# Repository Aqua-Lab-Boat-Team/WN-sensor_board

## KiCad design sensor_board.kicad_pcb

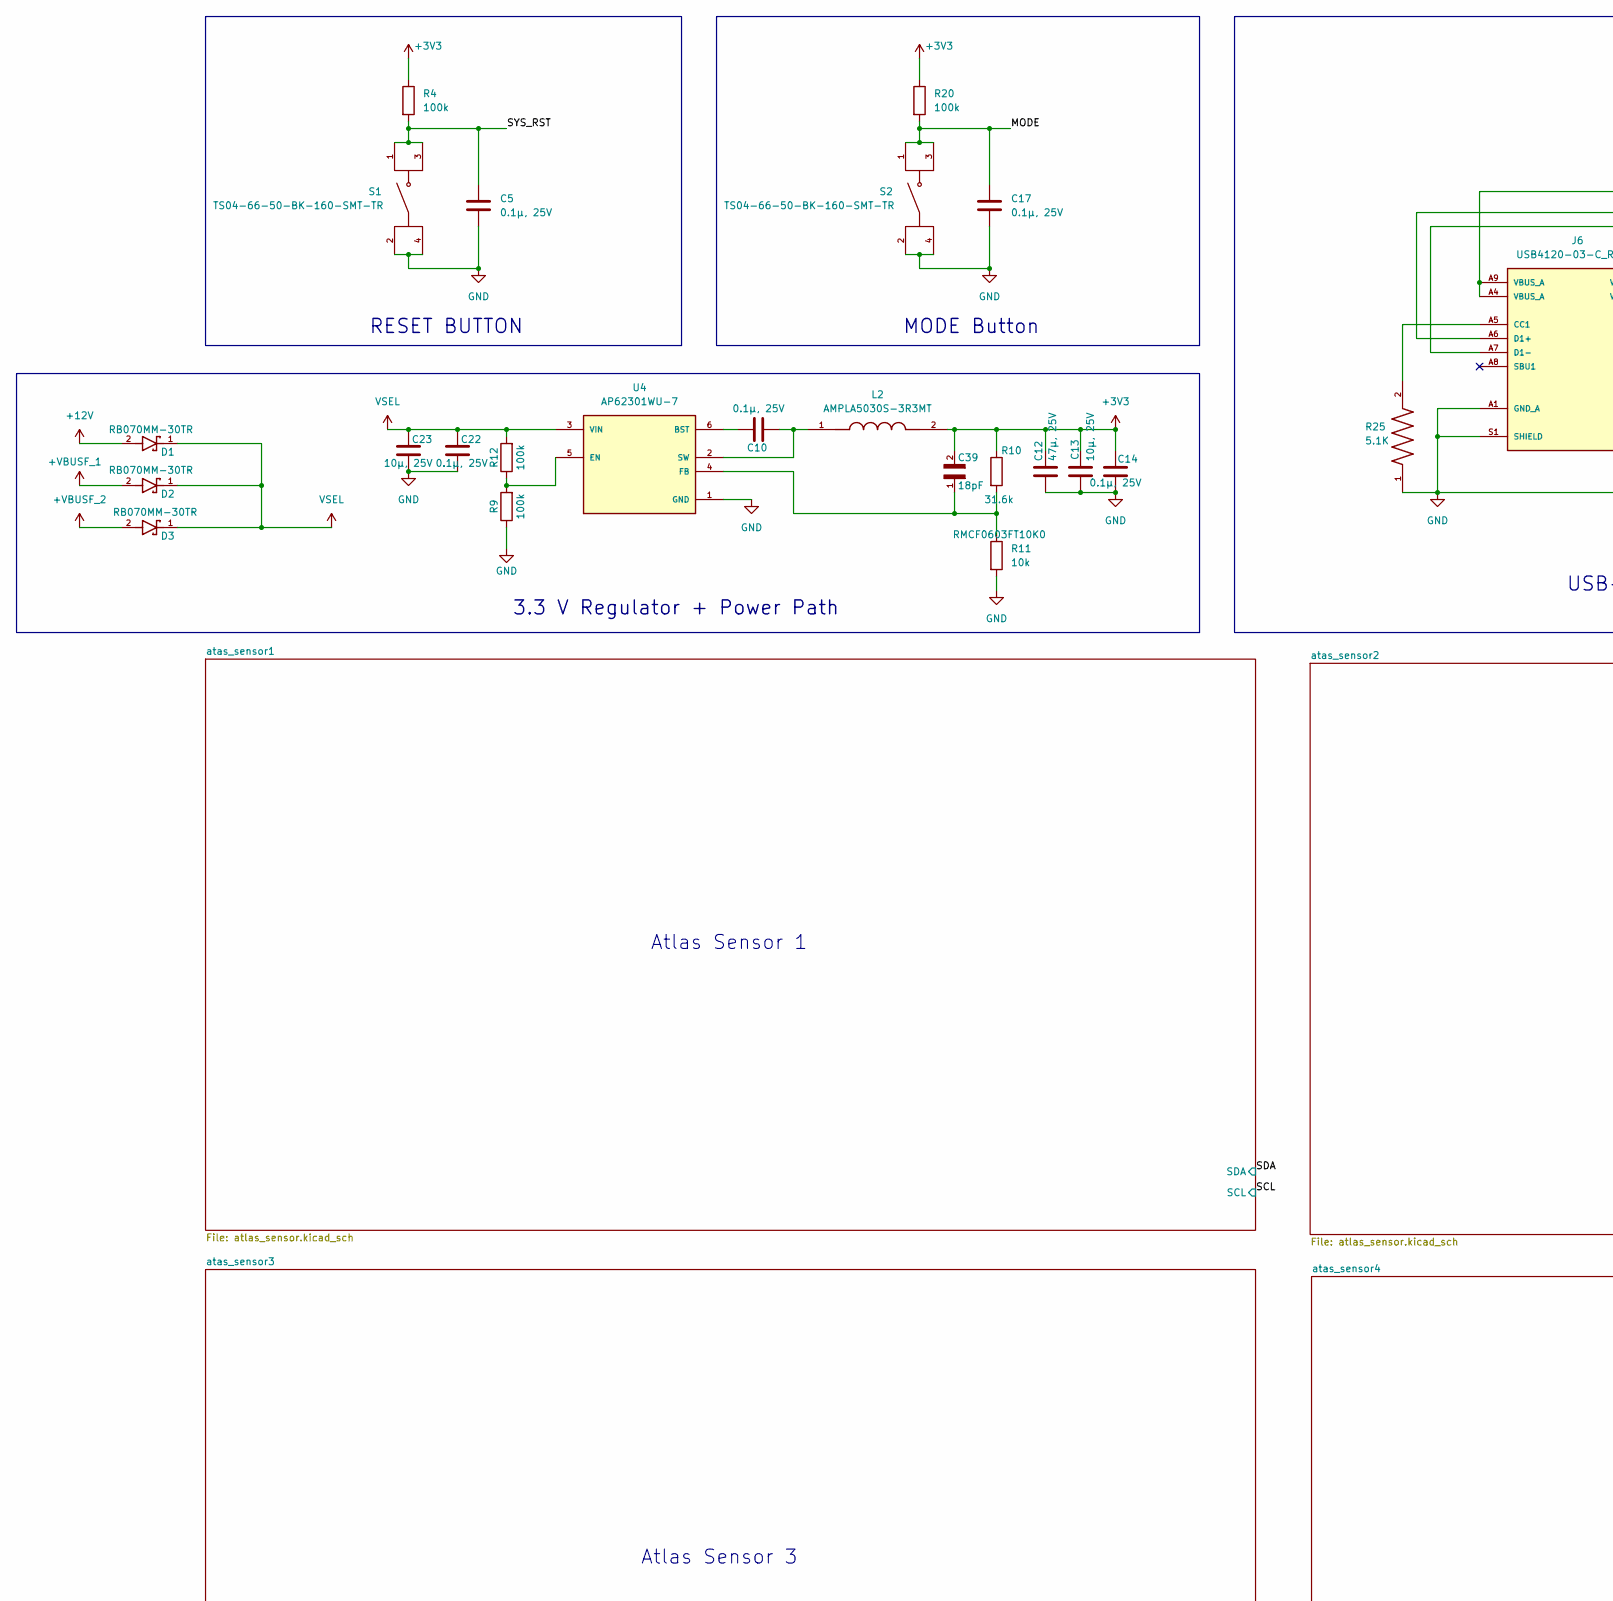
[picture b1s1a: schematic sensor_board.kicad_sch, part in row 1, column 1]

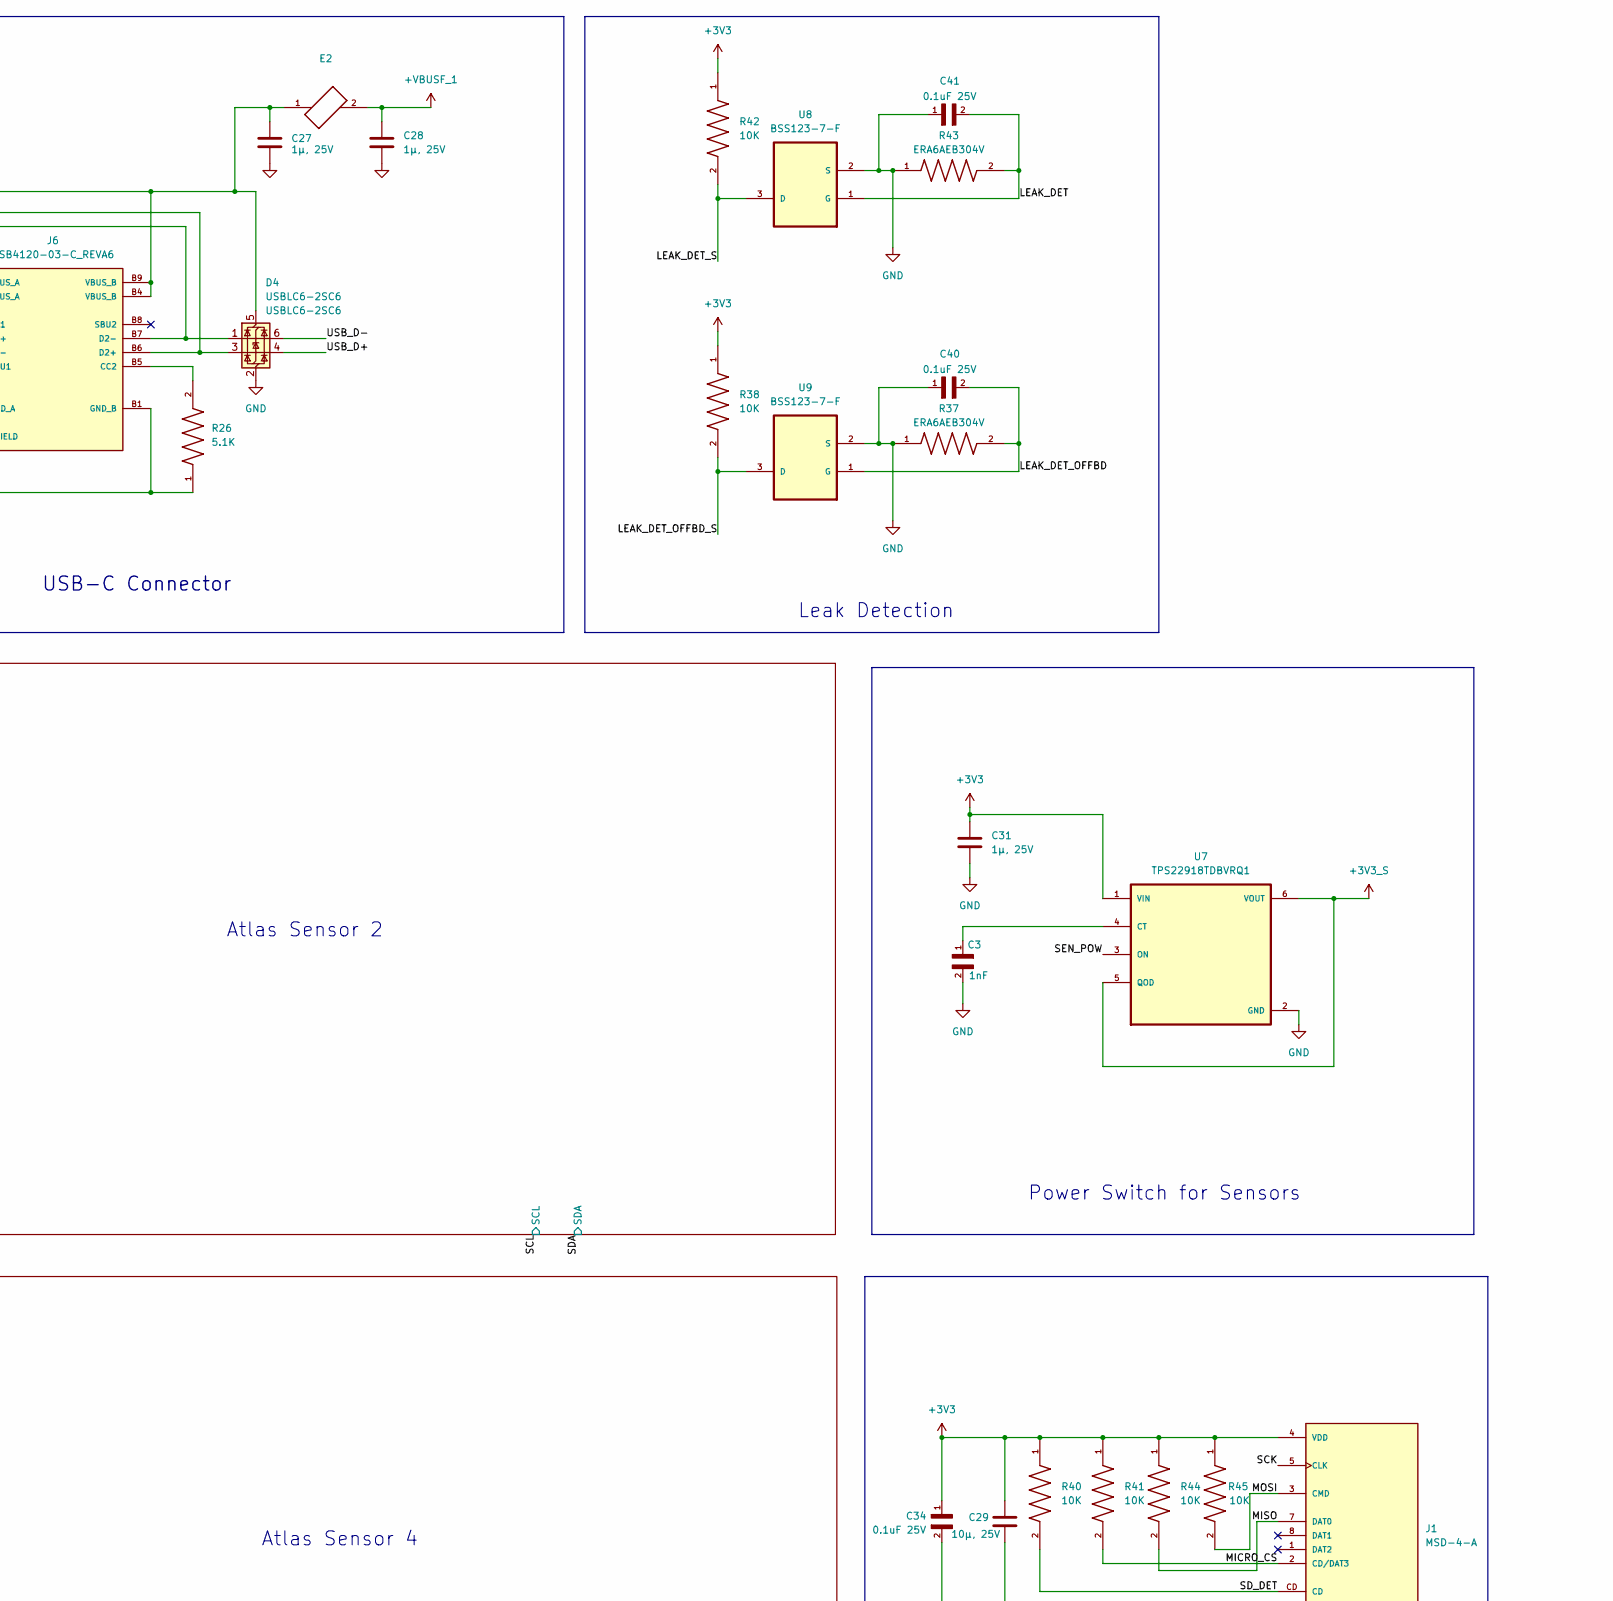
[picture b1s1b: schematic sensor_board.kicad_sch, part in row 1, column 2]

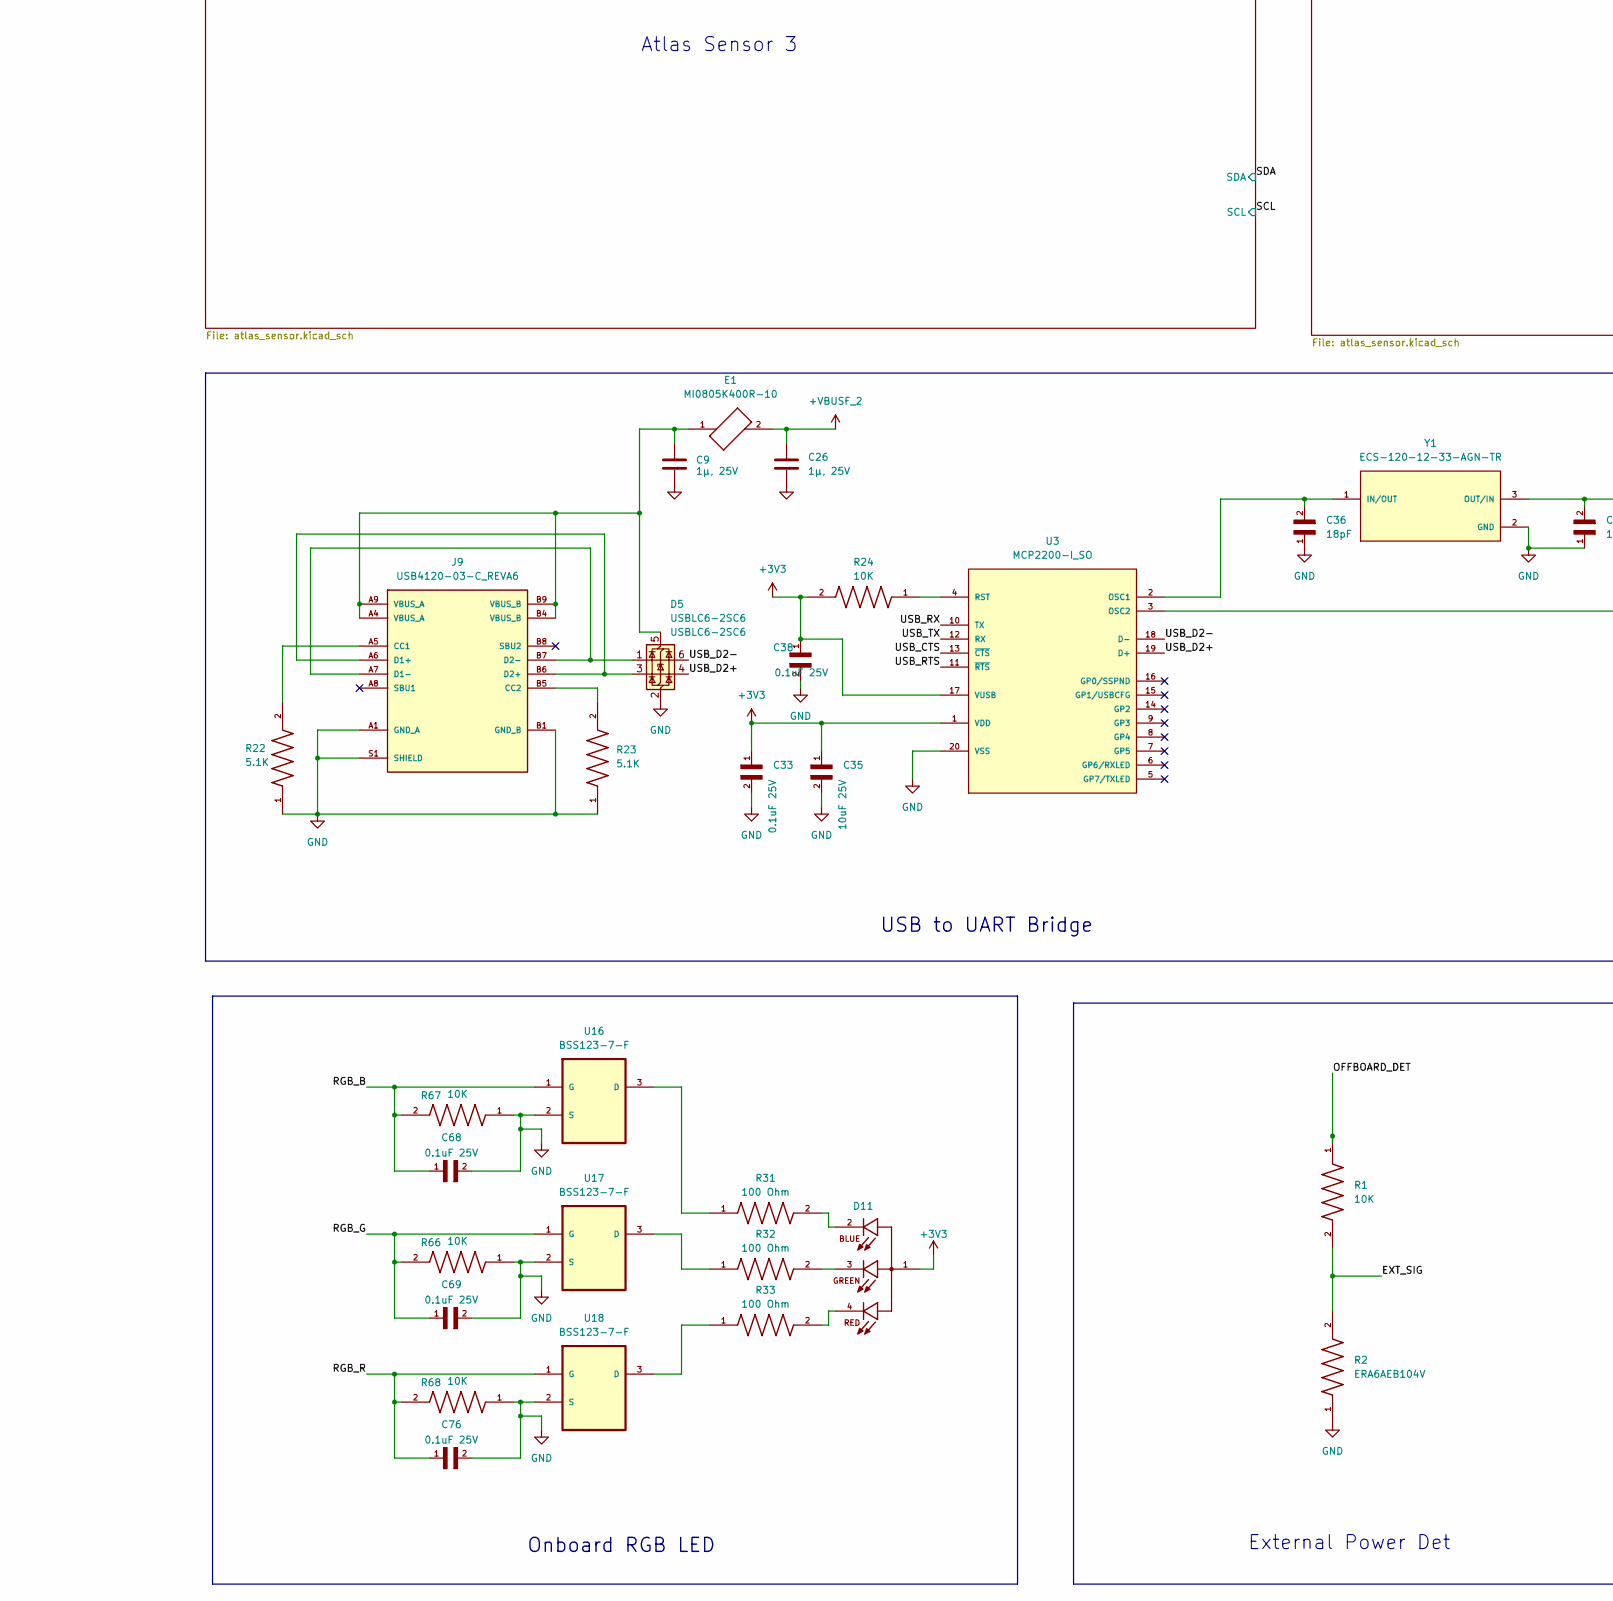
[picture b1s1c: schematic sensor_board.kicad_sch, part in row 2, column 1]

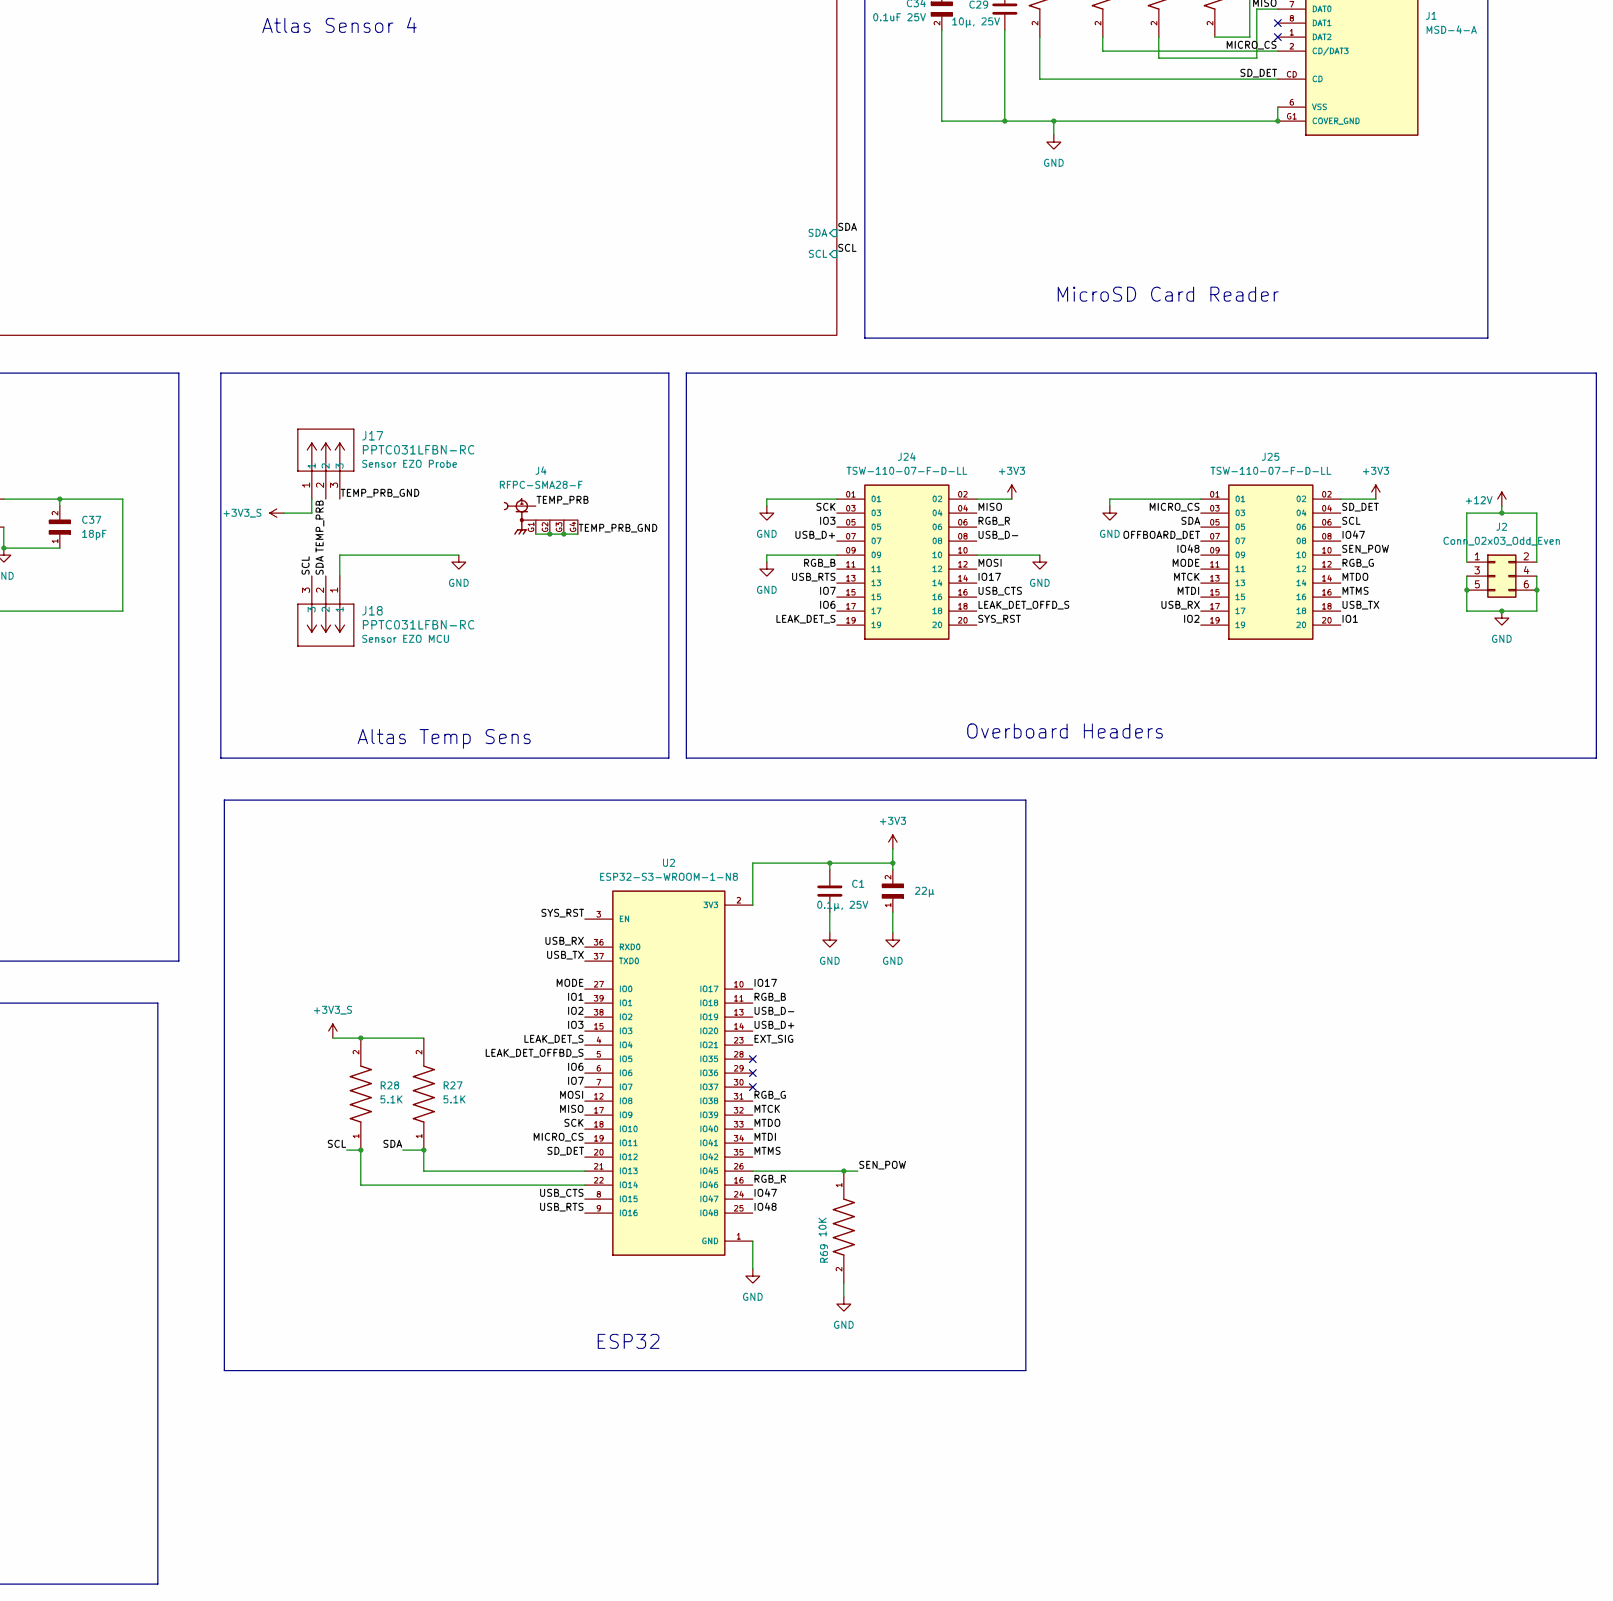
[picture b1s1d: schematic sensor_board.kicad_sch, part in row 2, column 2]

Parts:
C1, C5, C10, C14, C17, C22: 0.1µ, 25V; CAPC2012X95N
C2: 22µ; CAPC1608X105N
C3: 1nF; CAPC1608X90
C9, C26, C27, C28, C31: 1µ, 25V; CAPC2012X145N
C12: 47µ, 25V; CAPC3216X180N
C13, C23, C29: 10µ, 25V; CAPC2012X145N
C33, C34, C38, C40, C41, C68, C69, C76: 0.1uF 25V; CAPC2012X95N
C35: 10uF 25V; CAPC2012X145N
C36, C37, C39: 18pF; CAPC1608X90N
D1, D2, D3: RB070MM-30TR; DIO_RB070MM-30TR
D4, D5: USBLC6-2SC6; SOT-23-6
D11: CLMVC-FKA-CL1D1L71BB7C3C3; LED_CLMVC-FKA-CL1D1L71BB7C3C3; PARTREV 14
E1, E2: MI0805K400R-10; FB_MI0805K400R-10
J1: MSD-4-A; CUI_MSD-4-A; PARTREV 1.0
J2: Conn_02x03_Odd_Even; SULLINS_PPTC032LFBN-RC
J4: RFPC-SMA28-F; GRADCONN_RFPC-SMA28-F; PARTREV 1.0
J6, J9: USB4120-03-C_REVA6; GCT_USB4120-03-C_REVA6; PARTREV A6
J17, J18: PPTC031LFBN-RC; CONN_PPTC031_SUL
J24, J25: TSW-110-07-F-D-LL; SAMTEC_TSW-110-07-F-D-LL; PARTREV R
L2: AMPLA5030S-3R3MT; IND_AMPLA5030S-3R3MT; PARTREV 9/23/2019
R1, R24, R38, R40, R41, R42, R44, R45, R66, R67, R68, R69: 10K; RES_ERA6AEB103V; PARTREV 3/1/2020
R2: ERA6AEB104V; RES_ERA6AEB104V; PARTREV 3/1/2020
R4, R9, R12, R20: 100k; RES_ERA6AEB104V
R10: 31.6k; RES_ERA6AEB3162V
R11: 10k; RES_ERA6AEB103V
R22, R23, R25, R26, R27, R28: 5.1K; RESC1508X55N
R31, R32, R33: 100 Ohm; RES_ERJ3EKF1000V; PARTREV 3/1/2020
R37, R43: ERA6AEB304V; RES_ERA6AEB304V; PARTREV 3/1/2020
S1, S2: TS04-66-50-BK-160-SMT-TR; SW_TS04-66-50-BK-160-SMT-TR; PARTREV 1.04mm
U2: ESP32-S3-WROOM-1-N8; XCVR_ESP32-S3-WROOM-1-N8
U3: MCP2200-I_SO; SOIC20; MANUFACTURER_PART_NUMBER mcp2200-i/so
U4: AP62301WU-7; SOT95P280X100-6N; PARTREV Rev. 3 - 2
U7: TPS22918TDBVRQ1; SOT95P280X145-6N
U8, U9, U16, U17, U18: BSS123-7-F; SOT95P240X110-3N; MPN BSS123-7-F
Y1: ECS-120-12-33-AGN-TR; XTAL_ECS-120-12-33-AGN-TR

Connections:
+3V3: C1.1, C2.2, C12.1, C13.1, C14.1, C29.2, C31.1, C33.1, C34.1, C35.1, C38.1, C39.2, D11.1, J1.4 (VDD), J24.02, J25.02, L2.2, R4.1, R10.1, R20.1, R24.2, R38.1, R40.1, R41.1, R42.1, R44.1, R45.1, U2.2 (3V3), U3.1 (VDD), U3.17 (VUSB), U7.1 (VIN)
+3V3_S: J17.1, R27.2, R28.2, U7.5 (QOD), U7.6 (VOUT); also elsewhere on the board
+12V: D1.2, J2.1, J2.2
+VBUSF_1: C28.1, D2.2, E2.2
+VBUSF_2: C26.1, D3.2, E1.2
/IO1: J25.20, U2.39 (IO1)
/IO2: J25.19, U2.38 (IO2)
/IO3: J24.05, U2.15 (IO3)
/IO6: J24.17, U2.6 (IO6)
/IO7: J24.15, U2.7 (IO7)
/IO17: J24.14, U2.10 (IO17)
/IO47: J25.08, U2.24 (IO47)
/IO48: J25.09, U2.25 (IO48)
/LEAK_DET: C41.2, R43.2, U8.1 (G)
/LEAK_DET_OFFBD: C40.2, R37.2, U9.1 (G)
/LEAK_DET_S: J24.19, R42.2, U2.4 (IO4), U8.3 (D)
/MICRO_CS: J1.2 (CD/DAT3), J25.03, R41.2, U2.19 (IO11)
/MISO: J1.7 (DAT0), J24.04, R44.2, U2.17 (IO9)
/MODE: C17.1, J25.11, R20.2, S2.1, S2.3, U2.27 (IO0)
/MOSI: J1.3 (CMD), J24.12, R45.2, U2.12 (IO8)
/MTCK: J25.13, U2.32 (IO39)
/MTDI: J25.15, U2.34 (IO41)
/MTDO: J25.14, U2.33 (IO40)
/MTMS: J25.16, U2.35 (IO42)
/RGB_B: C68.1, J24.11, R67.2, U2.11 (IO18), U16.1 (G)
/RGB_G: C69.1, J25.12, R66.2, U2.31 (IO38), U17.1 (G)
/RGB_R: C76.1, J24.06, R68.2, U2.16 (IO46), U18.1 (G)
/SCK: J1.5 (CLK), J24.03, U2.18 (IO10)
/SCL: J18.3, J25.06, R28.1, U2.22 (IO14); also elsewhere on the board
/SDA: J18.2, J25.05, R27.1, U2.21 (IO13); also elsewhere on the board
/SD_DET: J1.CD, J25.04, R40.2, U2.20 (IO12)
/SEN_POW: J25.10, R69.1, U2.26 (IO45), U7.3 (ON)
/SYS_RST: C5.1, J24.20, R4.2, S1.1, S1.3, U2.3 (EN)
/TEMP_PRB: J4.1, J17.2
/TEMP_PRB_GND: J4.G1, J4.G2, J4.G3, J4.G4, J17.3
/USB_CTS: J24.16, U2.8 (IO15), U3.13 (~CTS)
/USB_D2+: D5.4 (I/O2), U3.19 (D+)
/USB_D2-: D5.6 (I/O1), U3.18 (D-)
/USB_D+: D4.4 (I/O2), J24.07, U2.14 (IO20)
/USB_D-: D4.6 (I/O1), J24.08, U2.13 (IO19)
/USB_RTS: J24.13, U2.9 (IO16), U3.11 (~RTS)
/USB_RX: J25.17, U2.36 (RXD0), U3.10 (TX)
/USB_TX: J25.18, U2.37 (TXD0), U3.12 (RX)
GND: C1.2, C2.1, C3.2, C5.2, C9.2, C12.2, C13.2, C14.2, C17.2, C22.2, C23.2, C26.2, C27.2, C28.2, C29.1, C31.2, C33.2, C34.2, C35.2, C36.1, C37.1, C38.2, C40.1, C41.1, C68.2, C69.2, C76.2, D4.2 (GND), D5.2 (GND), J1.6 (VSS), J1.G1 (COVER_GND), J1.G2 (COVER_GND), J1.G3 (COVER_GND), J1.G4 (COVER_GND), J2.3, J2.4, J2.5, J2.6, J6.A1 (GND_A), J6.A12 (GND_A), J6.B1 (GND_B), J6.B12 (GND_B), J6.S1 (SHIELD), J6.S2 (SHIELD), J6.S3 (SHIELD), J6.S4 (SHIELD), J9.A1 (GND_A), J9.A12 (GND_A), J9.B1 (GND_B), J9.B12 (GND_B), J9.S1 (SHIELD), J9.S2 (SHIELD), J9.S3 (SHIELD), J9.S4 (SHIELD), J18.1, J24.01, J24.09, J24.10, J25.01, R2.1, R9.1, R11.2, R22.1, R23.1, R25.1, R26.1, R37.1, R43.1, R66.1, R67.1, R68.1, R69.2, S1.2, S1.4, S2.2, S2.4, U2.1 (GND), U2.40 (GND), U2.41, U2.41_1 (GND), U2.41_2 (GND), U2.41_3 (GND), U2.41_4 (GND), U2.41_5 (GND), U2.41_6 (GND), U2.41_7 (GND), U2.41_8 (GND), U2.41_9 (GND), U3.20 (VSS), U4.1 (GND), U7.2 (GND), U8.2 (S), U9.2 (S), U16.2 (S), U17.2 (S), U18.2 (S), Y1.2 (GND), Y1.4 (GND); also elsewhere on the board
unnamed: C27.1, D4.5 (VBUS), E2.1, J6.A4 (VBUS_A), J6.A9 (VBUS_A), J6.B4 (VBUS_B), J6.B9 (VBUS_B)
unnamed: C9.1, D5.5 (VBUS), E1.1, J9.A4 (VBUS_A), J9.A9 (VBUS_A), J9.B4 (VBUS_B), J9.B9 (VBUS_B)
unnamed: D11.2, R31.2
unnamed: D11.3, R32.2
unnamed: D11.4, R33.2
unnamed: J6.A5 (CC1), R25.2
unnamed: J6.B5 (CC2), R26.2
unnamed: D4.3 (I/O2), J6.A6 (D1+), J6.B6 (D2+)
unnamed: D4.1 (I/O1), J6.A7 (D1-), J6.B7 (D2-)
unnamed: J9.A5 (CC1), R22.2
unnamed: J9.B5 (CC2), R23.2
unnamed: D5.3 (I/O2), J9.A6 (D1+), J9.B6 (D2+)
unnamed: D5.1 (I/O1), J9.A7 (D1-), J9.B7 (D2-)
unnamed: C36.2, U3.2 (OSC1), Y1.1 (IN/OUT)
unnamed: C37.2, U3.3 (OSC2), Y1.3 (OUT/IN)
unnamed: R24.1, U3.4 (RST)
unnamed: C10.1, U4.6 (BST)
unnamed: R9.2, R12.1, U4.5 (EN)
unnamed: C39.1, R10.2, R11.1, U4.4 (FB)
unnamed: C10.2, L2.1, U4.2 (SW)
unnamed: C3.1, U7.4 (CT)
unnamed: R31.1, U16.3 (D)
unnamed: R32.1, U17.3 (D)
unnamed: R33.1, U18.3 (D)
VSEL: C22.1, C23.1, D1.1, D2.1, D3.1, R12.2, U4.3 (VIN)

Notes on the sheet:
USB-C Connector
Atlas Sensor 1
ESP32
Leak Detection
Overboard Headers
MODE Button
RESET BUTTON
Onboard RGB LED
MicroSD Card Reader
External Power Det
Atlas Sensor 4
Atlas Sensor 2
Altas Temp Sens
USB to UART Bridge
Power Switch for Sensors
3.3 V Regulator + Power Path
Atlas Sensor 3

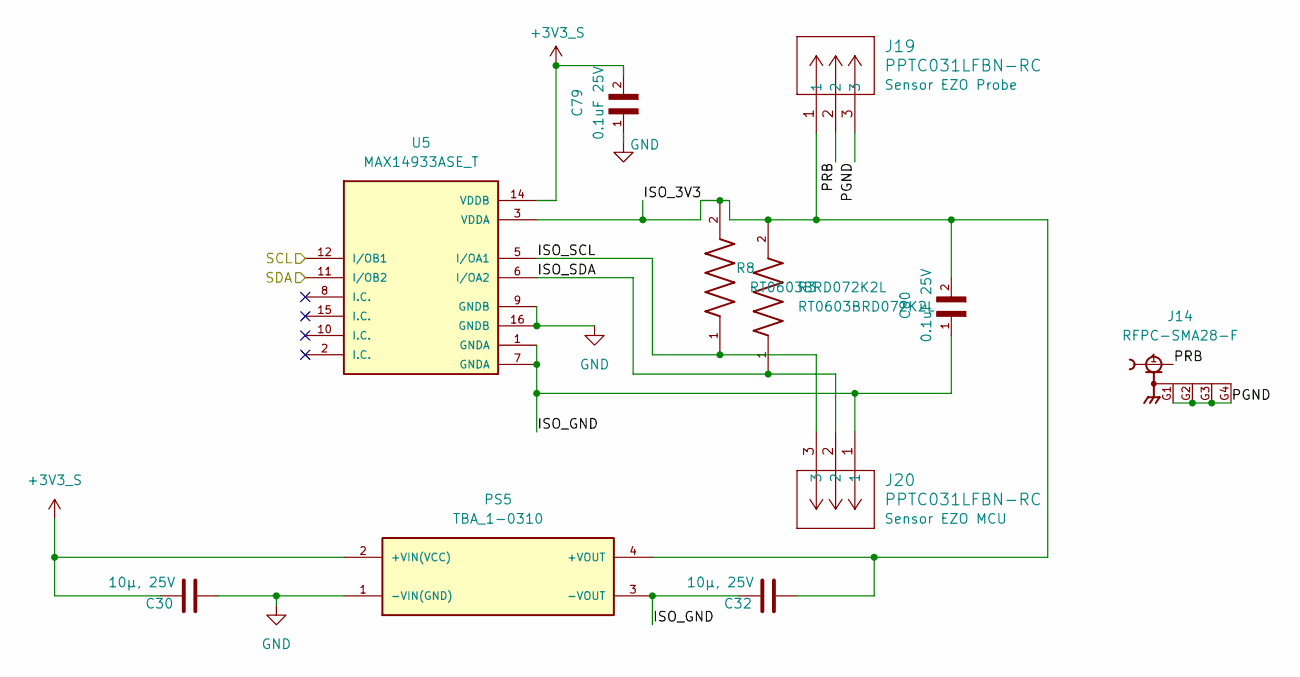
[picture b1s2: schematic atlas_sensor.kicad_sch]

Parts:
C30, C32: 10µ, 25V; CAPC2012X145N
C79, C80: 0.1uF 25V; CAPC2012X95N
J14: RFPC-SMA28-F; GRADCONN_RFPC-SMA28-F; PARTREV 1.0
J19, J20: PPTC031LFBN-RC; CONN_PPTC031_SUL
PS5: TBA_1-0310; CONV_TBA_1-0310; PARTREV April 19, 2021
R3, R8: RT0603BRD072K2L; RESC1608X55N
U5: MAX14933ASE_T; SOIC127P600X175-16N

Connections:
+3V3_S: C30.1, C79.2, PS5.2 (+VIN(VCC)), U5.14 (VDDB); also elsewhere on the board
/SCL: U5.12 (I/OB1); also elsewhere on the board
/SDA: U5.11 (I/OB2); also elsewhere on the board
/atas_sensor1/ISO_3V3: C32.2, C80.2, J19.1, PS5.4 (+VOUT), U5.3 (VDDA); also elsewhere on the board
/atas_sensor1/ISO_GND: C32.1, C80.1, J20.1, PS5.3 (-VOUT), U5.1 (GNDA), U5.7 (GNDA)
/atas_sensor1/ISO_SCL: J20.3, U5.5 (I/OA1); also elsewhere on the board
/atas_sensor1/ISO_SDA: J20.2, U5.6 (I/OA2); also elsewhere on the board
/atas_sensor1/PGND: J14.G1, J14.G2, J14.G3, J14.G4, J19.3
/atas_sensor1/PRB: J14.1, J19.2
GND: C30.2, C79.1, PS5.1 (-VIN(GND)), U5.9 (GNDB), U5.16 (GNDB); also elsewhere on the board

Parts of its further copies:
C42, C43, C44, C45, C46, C47: 10µ, 25V; CAPC2012X145N
C81, C82, C83, C84, C85, C86: 0.1uF 25V; CAPC2012X95N
J15, J16, J29: RFPC-SMA28-F; GRADCONN_RFPC-SMA28-F; PARTREV 1.0
J21, J22, J23, J26, J27, J28: PPTC031LFBN-RC; CONN_PPTC031_SUL
PS6, PS7, PS8: TBA_1-0310; CONV_TBA_1-0310; PARTREV April 19, 2021
U6, U10, U11: MAX14933ASE_T; SOIC127P600X175-16N

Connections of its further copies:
+3V3_S: C42.1, C44.1, C46.1, C81.2, C83.2, C85.2, PS6.2 (+VIN(VCC)), PS7.2 (+VIN(VCC)), PS8.2 (+VIN(VCC)), U6.14 (VDDB), U10.14 (VDDB), U11.14 (VDDB); also elsewhere on the board
/SCL: U6.12 (I/OB1), U10.12 (I/OB1), U11.12 (I/OB1); also elsewhere on the board
/SDA: U6.11 (I/OB2), U10.11 (I/OB2), U11.11 (I/OB2); also elsewhere on the board
/atas_sensor2/ISO_3V3: C47.2, C86.2, J27.1, PS8.4 (+VOUT), U11.3 (VDDA); also elsewhere on the board
/atas_sensor2/ISO_GND: C47.1, C86.1, J28.1, PS8.3 (-VOUT), U11.1 (GNDA), U11.7 (GNDA)
/atas_sensor2/ISO_SCL: J28.3, U11.5 (I/OA1); also elsewhere on the board
/atas_sensor2/ISO_SDA: J28.2, U11.6 (I/OA2); also elsewhere on the board
/atas_sensor2/PGND: J15.G1, J15.G2, J15.G3, J15.G4, J27.3
/atas_sensor2/PRB: J15.1, J27.2
/atas_sensor3/ISO_3V3: C43.2, C82.2, J21.1, PS6.4 (+VOUT), U6.3 (VDDA); also elsewhere on the board
/atas_sensor3/ISO_GND: C43.1, C82.1, J22.1, PS6.3 (-VOUT), U6.1 (GNDA), U6.7 (GNDA)
/atas_sensor3/ISO_SCL: J22.3, U6.5 (I/OA1); also elsewhere on the board
/atas_sensor3/ISO_SDA: J22.2, U6.6 (I/OA2); also elsewhere on the board
/atas_sensor3/PGND: J16.G1, J16.G2, J16.G3, J16.G4, J21.3
/atas_sensor3/PRB: J16.1, J21.2
/atas_sensor4/ISO_3V3: C45.2, C84.2, J23.1, PS7.4 (+VOUT), U10.3 (VDDA); also elsewhere on the board
/atas_sensor4/ISO_GND: C45.1, C84.1, J26.1, PS7.3 (-VOUT), U10.1 (GNDA), U10.7 (GNDA)
/atas_sensor4/ISO_SCL: J26.3, U10.5 (I/OA1); also elsewhere on the board
/atas_sensor4/ISO_SDA: J26.2, U10.6 (I/OA2); also elsewhere on the board
/atas_sensor4/PGND: J23.3, J29.G1, J29.G2, J29.G3, J29.G4
/atas_sensor4/PRB: J23.2, J29.1
GND: C42.2, C44.2, C46.2, C81.1, C83.1, C85.1, PS6.1 (-VIN(GND)), PS7.1 (-VIN(GND)), PS8.1 (-VIN(GND)), U6.9 (GNDB), U6.16 (GNDB), U10.9 (GNDB), U10.16 (GNDB), U11.9 (GNDB), U11.16 (GNDB); also elsewhere on the board

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
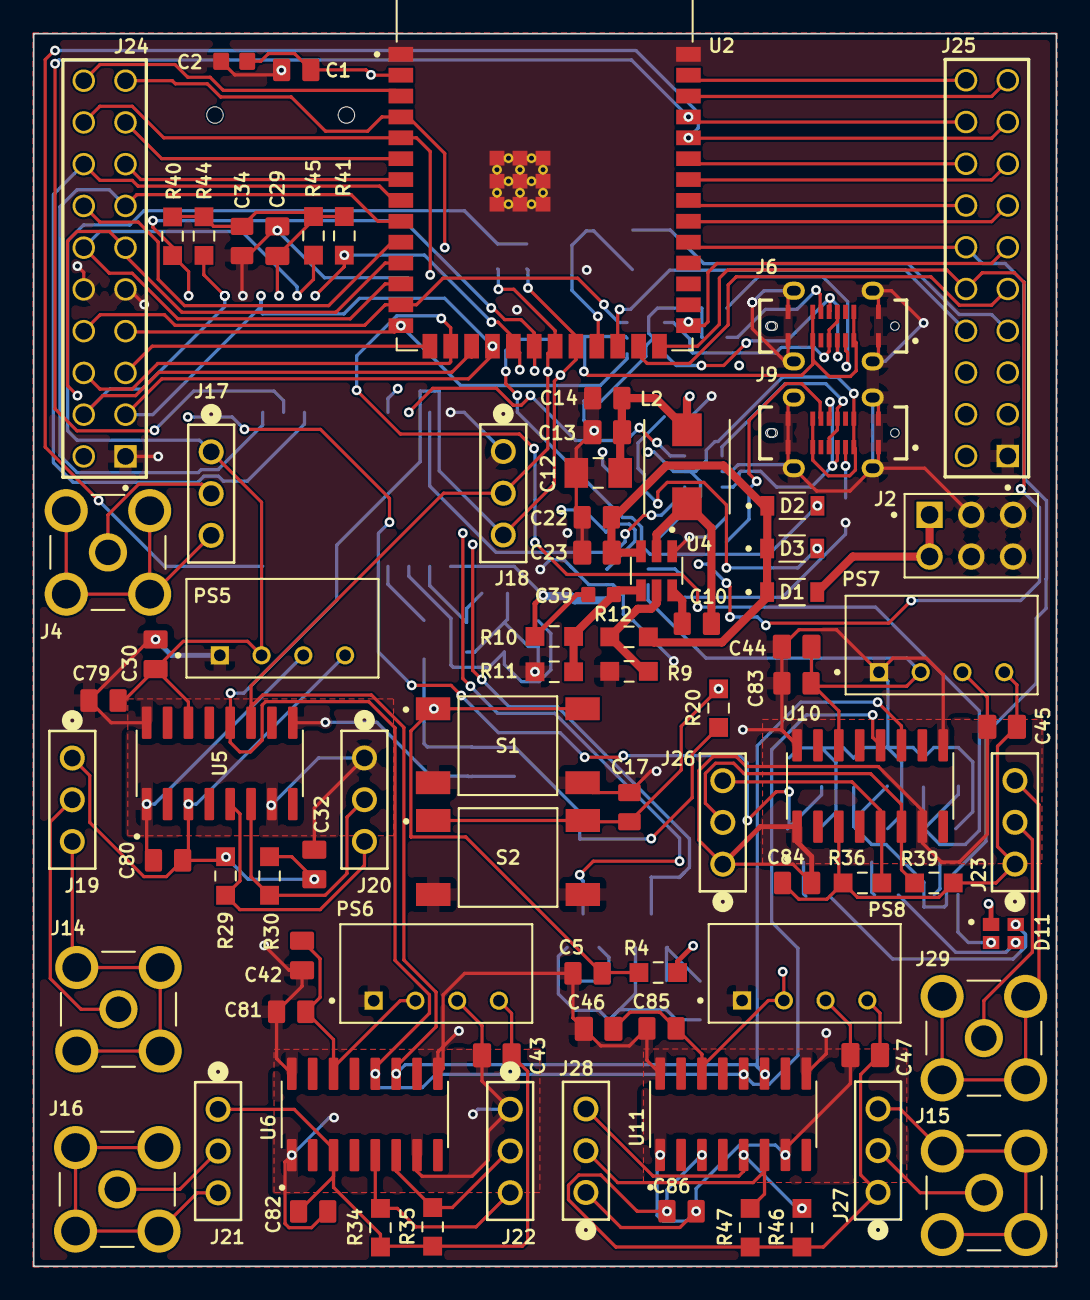
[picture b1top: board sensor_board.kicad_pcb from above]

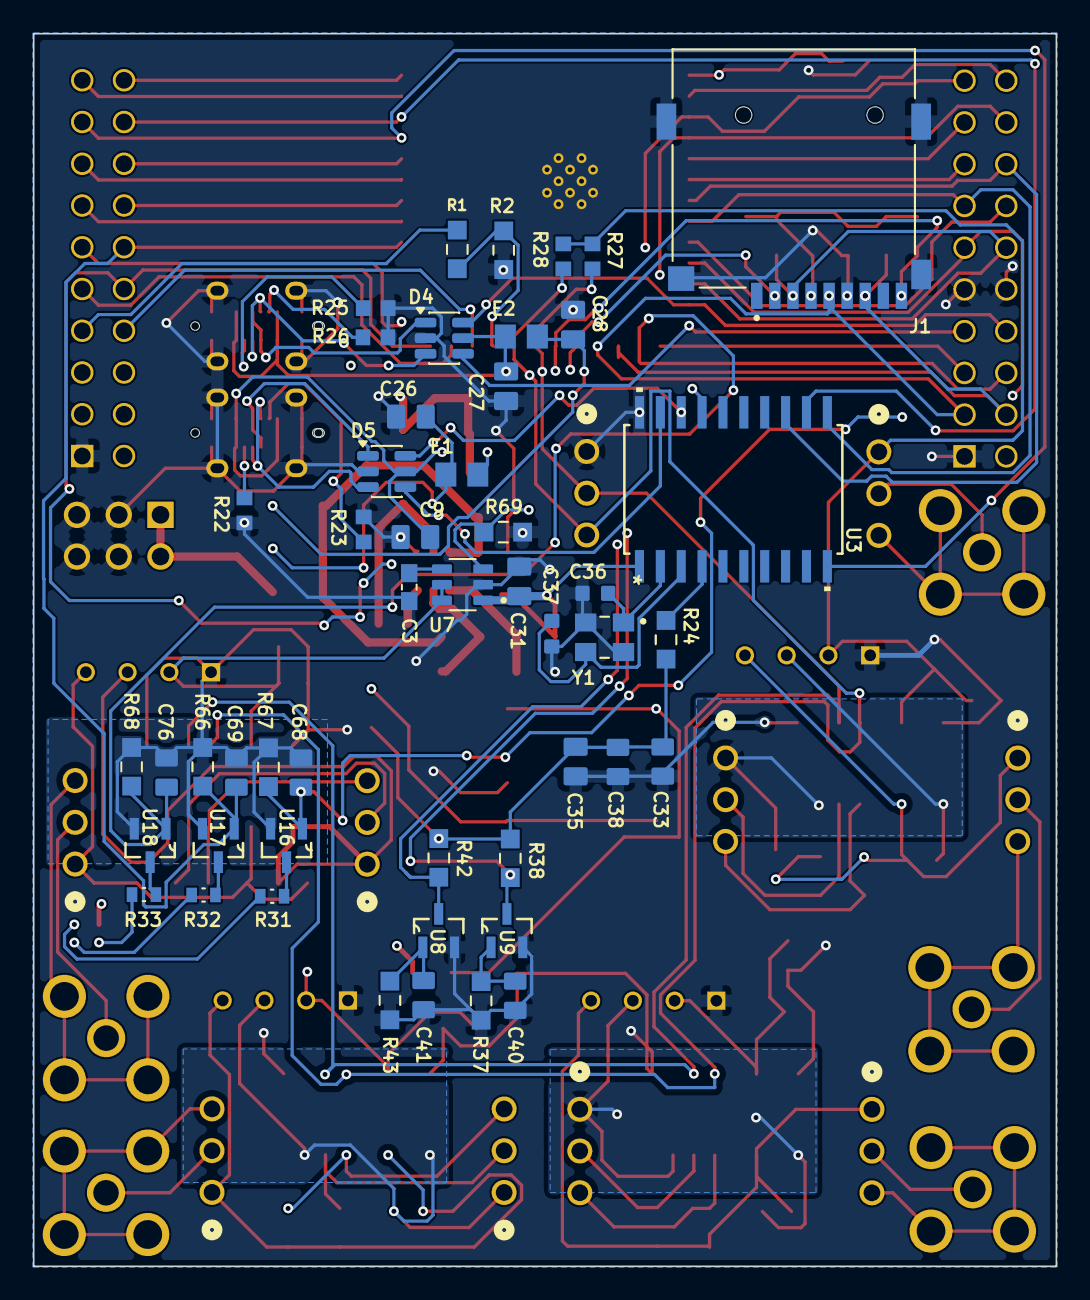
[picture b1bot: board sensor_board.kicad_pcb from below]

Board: 4 copper layers, 62.2 x 75.0 mm, 133 parts (49 on the bottom side), 96 nets.

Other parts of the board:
R29, R30, R34, R35, R36, R39, R46, R47: 10k; RES_ERA6AEB103V

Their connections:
/atas_sensor1/ISO_3V3: R29.1, R30.1; also elsewhere on the board
/atas_sensor1/ISO_SCL: R29.2; also elsewhere on the board
/atas_sensor1/ISO_SDA: R30.2; also elsewhere on the board
/atas_sensor2/ISO_3V3: R46.1, R47.1; also elsewhere on the board
/atas_sensor2/ISO_SCL: R46.2; also elsewhere on the board
/atas_sensor2/ISO_SDA: R47.2; also elsewhere on the board
/atas_sensor3/ISO_3V3: R34.1, R35.1; also elsewhere on the board
/atas_sensor3/ISO_SCL: R34.2; also elsewhere on the board
/atas_sensor3/ISO_SDA: R35.2; also elsewhere on the board
/atas_sensor4/ISO_3V3: R36.1, R39.1; also elsewhere on the board
/atas_sensor4/ISO_SCL: R36.2; also elsewhere on the board
/atas_sensor4/ISO_SDA: R39.2; also elsewhere on the board

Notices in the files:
parts and their libraries:
COPYRIGHT: Copyright (C) 2024 Ultra Librarian. All rights reserved.
COPYRIGHT: Copyright (C) 2023 Ultra Librarian. All rights reserved.
